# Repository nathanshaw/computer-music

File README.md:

Setup will be as follows

IAC MIDI BUS SHOUDLD BE CREATED ON MAC

CHANNELS 1-8 ARE THE FLOPPY DRIVES ON THE FIRST BUS
- pitched around C0-A3
- taken care of via an instance of MOPPY running on computer
- two arduino UNO's connected to mac VIA USB

CHANNELS 9-12 ARE THE CDROM DRIVES ON THE FIRST BUS
- midi notes split around 64 moving motor one way or another
- taken care of via python
- one arduino MEGA takes care of these 

CHANNELS 13-16 ARE THE CDROM DRIVE TREYS ON THE FIRST BUS
- any message sent will trigger the tray

CHANNELS 1-4 ARE THE STEPPERS ON THE SECOND BUS
- midi notes split around 64 moving the motor one way or another
- taken care of via python
- one arduino MEGA takes care of these 

PREREQUISITES:

sudo apt-get install python-dev libxml2-dev libxslt-dev
sudo apt-get install libasound2-dev
easy_install rtmidi-python
sudo apt-get install jack-tools ant openjdk-7-jdk fftw3 qjackctl
rtmidi python binding - pip install rtmidi-python
sudo pip install git-python
sudo pip install jira

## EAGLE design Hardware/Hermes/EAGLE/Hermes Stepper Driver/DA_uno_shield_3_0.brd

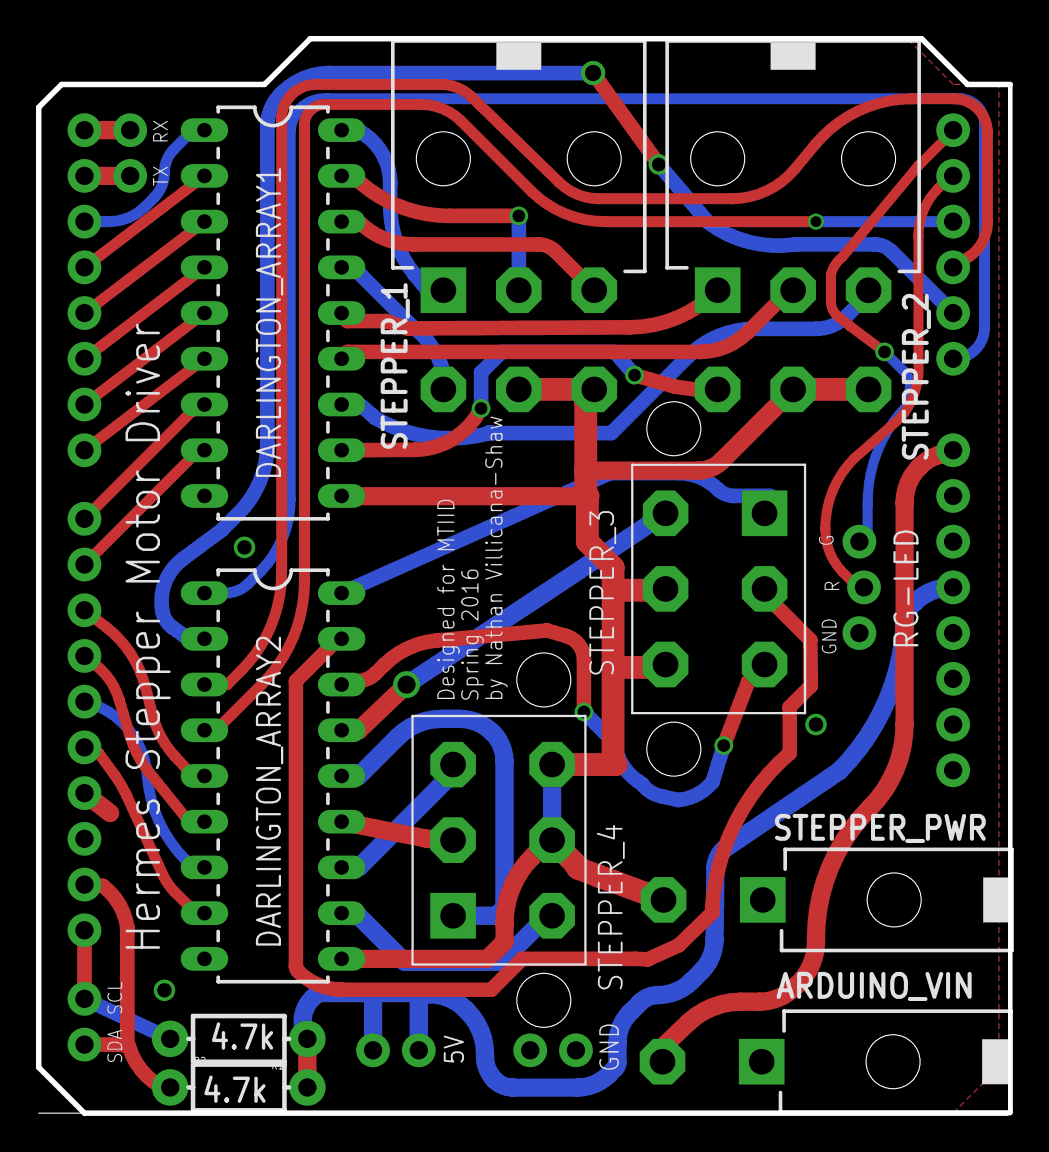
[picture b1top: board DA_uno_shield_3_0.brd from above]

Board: 2 copper layers, 54.0 x 59.7 mm, 16 parts (0 on the bottom side), 42 nets.

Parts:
5V: 1X02_NO_SILK
ARDUINO: ARDUINO_R3_SHIELD; UNO_R3_SHIELD
ARDUINO_VIN: 39-30-02?_S; 39-30-?02?
DARLINGTON_ARRAY1, DARLINGTON_ARRAY2: DIL18
GND: 1X02_NO_SILK
I2C: 1X02_NO_SILK
R1, R2: 4.7k; AXIAL-0.3-KIT
RG-LED: 1X03_LOCK_NO_SILK
SPI: 1X02_NO_SILK
STEPPER_1, STEPPER_2: 39-30-06?_S; 39-30-?06?
STEPPER_3, STEPPER_4: 39-29-06?; 39-29-?06?
STEPPER_PWR: 39-30-02?_S; 39-30-?02?

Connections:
5V: 5V.1, 5V.2, ARDUINO.5V, R1.P$1, R2.P$2
A0: ARDUINO.A0, DARLINGTON_ARRAY2.1
A1: ARDUINO.A1, DARLINGTON_ARRAY2.2
A2: ARDUINO.A2, DARLINGTON_ARRAY2.3
A3: ARDUINO.A3, DARLINGTON_ARRAY2.4
A4: ARDUINO.A4, RG-LED.2
A5: ARDUINO.A5, RG-LED.3
D10: ARDUINO.D10, DARLINGTON_ARRAY2.5
D11: ARDUINO.D11, DARLINGTON_ARRAY2.6
D12: ARDUINO.D12, DARLINGTON_ARRAY2.7
D13: ARDUINO.D13, DARLINGTON_ARRAY2.8
GND: ARDUINO.GND@0, ARDUINO.GND@1, ARDUINO.GND@2, ARDUINO_VIN.1, DARLINGTON_ARRAY1.9, DARLINGTON_ARRAY2.9, GND.1, GND.2, RG-LED.1, STEPPER_PWR.1
unnamed: DARLINGTON_ARRAY1.14, STEPPER_2.1
unnamed: DARLINGTON_ARRAY1.13, STEPPER_2.2
unnamed: DARLINGTON_ARRAY1.12, STEPPER_2.3
unnamed: DARLINGTON_ARRAY1.11, STEPPER_2.4
unnamed: ARDUINO.D6, DARLINGTON_ARRAY1.5
unnamed: ARDUINO.D7, DARLINGTON_ARRAY1.6
unnamed: ARDUINO.D8, DARLINGTON_ARRAY1.7
unnamed: ARDUINO.D9, DARLINGTON_ARRAY1.8
unnamed: DARLINGTON_ARRAY2.18, STEPPER_3.P$1
unnamed: ARDUINO.D2, DARLINGTON_ARRAY1.1
unnamed: DARLINGTON_ARRAY1.18, STEPPER_1.1
unnamed: DARLINGTON_ARRAY1.17, STEPPER_1.2
unnamed: DARLINGTON_ARRAY1.16, STEPPER_1.3
unnamed: DARLINGTON_ARRAY1.15, STEPPER_1.4
unnamed: ARDUINO.D3, DARLINGTON_ARRAY1.2
unnamed: ARDUINO.D4, DARLINGTON_ARRAY1.3
unnamed: ARDUINO.D5, DARLINGTON_ARRAY1.4
unnamed: DARLINGTON_ARRAY2.17, STEPPER_3.P$2
unnamed: DARLINGTON_ARRAY2.16, STEPPER_3.P$3
unnamed: DARLINGTON_ARRAY2.15, STEPPER_3.P$4
unnamed: DARLINGTON_ARRAY2.14, STEPPER_4.P$1
unnamed: DARLINGTON_ARRAY2.13, STEPPER_4.P$2
unnamed: DARLINGTON_ARRAY2.12, STEPPER_4.P$3
unnamed: DARLINGTON_ARRAY2.11, STEPPER_4.P$4
RX: ARDUINO.RX, SPI.1
SCL: ARDUINO.SCL, I2C.2, R1.P$2
SDA: ARDUINO.SDA, I2C.1, R2.P$1
TX: ARDUINO.TX, SPI.2
VCC: DARLINGTON_ARRAY1.10, DARLINGTON_ARRAY2.10, STEPPER_1.5, STEPPER_1.6, STEPPER_2.5, STEPPER_2.6, STEPPER_3.P$5, STEPPER_3.P$6, STEPPER_4.P$5, STEPPER_4.P$6, STEPPER_PWR.2
VIN: ARDUINO.VIN, ARDUINO_VIN.2

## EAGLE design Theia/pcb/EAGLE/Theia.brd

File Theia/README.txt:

The Theia board is an Arduino Uno shield that supports up to
8 SR-04 Ultrasonic Rangefinders.

Theia is a greek goddess and is directly translated from greek to mean “goddess” or 
“divine”. She is the mother of Helios, Selene and Eos the gods of the sun, the moon and the dawn respectively. She is the eldest daughter of Gaia and Uranus the gods of the Earth and Sky, giving her a primal origin.

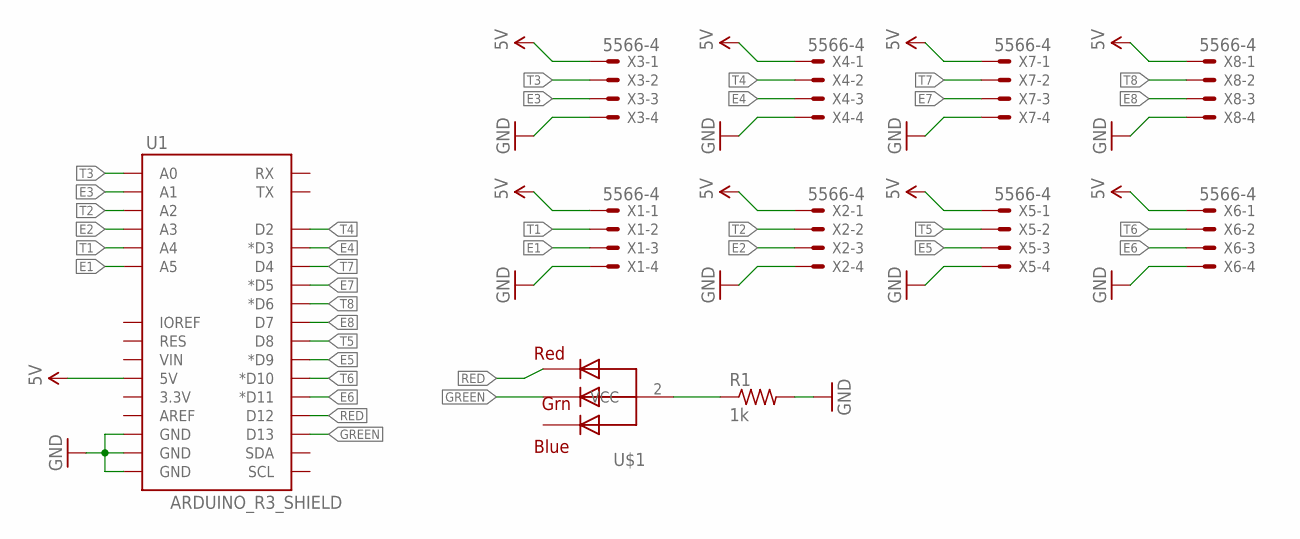
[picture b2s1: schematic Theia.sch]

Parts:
R1: 1k; 0207/7
U1: ARDUINO_R3_SHIELD; UNO_R3_SHIELD
U$1: RGBLED_CA; LED5MMRGB
X1, X2, X3, X4, X5, X6, X7, X8: 5566-4

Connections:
5V: U1.5V, X1.1, X2.1, X3.1, X4.1, X5.1, X6.1, X7.1, X8.1
E1: U1.A5, X1.3
E2: U1.A3, X2.3
E3: U1.A1, X3.3
E4: U1.D3 (*D3), X4.3
E5: U1.D9 (*D9), X5.3
E6: U1.D11 (*D11), X6.3
E7: U1.D5 (*D5), X7.3
E8: U1.D7, X8.3
GND: R1.2, U1.GND@0 (GND), U1.GND@1 (GND), U1.GND@2 (GND), X1.4, X2.4, X3.4, X4.4, X5.4, X6.4, X7.4, X8.4
GREEN: U1.D13, U$1.3 (GREEN)
unnamed: R1.1, U$1.2 (VCC)
RED: U1.D12, U$1.1 (RED)
T1: U1.A4, X1.2
T2: U1.A2, X2.2
T3: U1.A0, X3.2
T4: U1.D2, X4.2
T5: U1.D8, X5.2
T6: U1.D10 (*D10), X6.2
T7: U1.D4, X7.2
T8: U1.D6 (*D6), X8.2

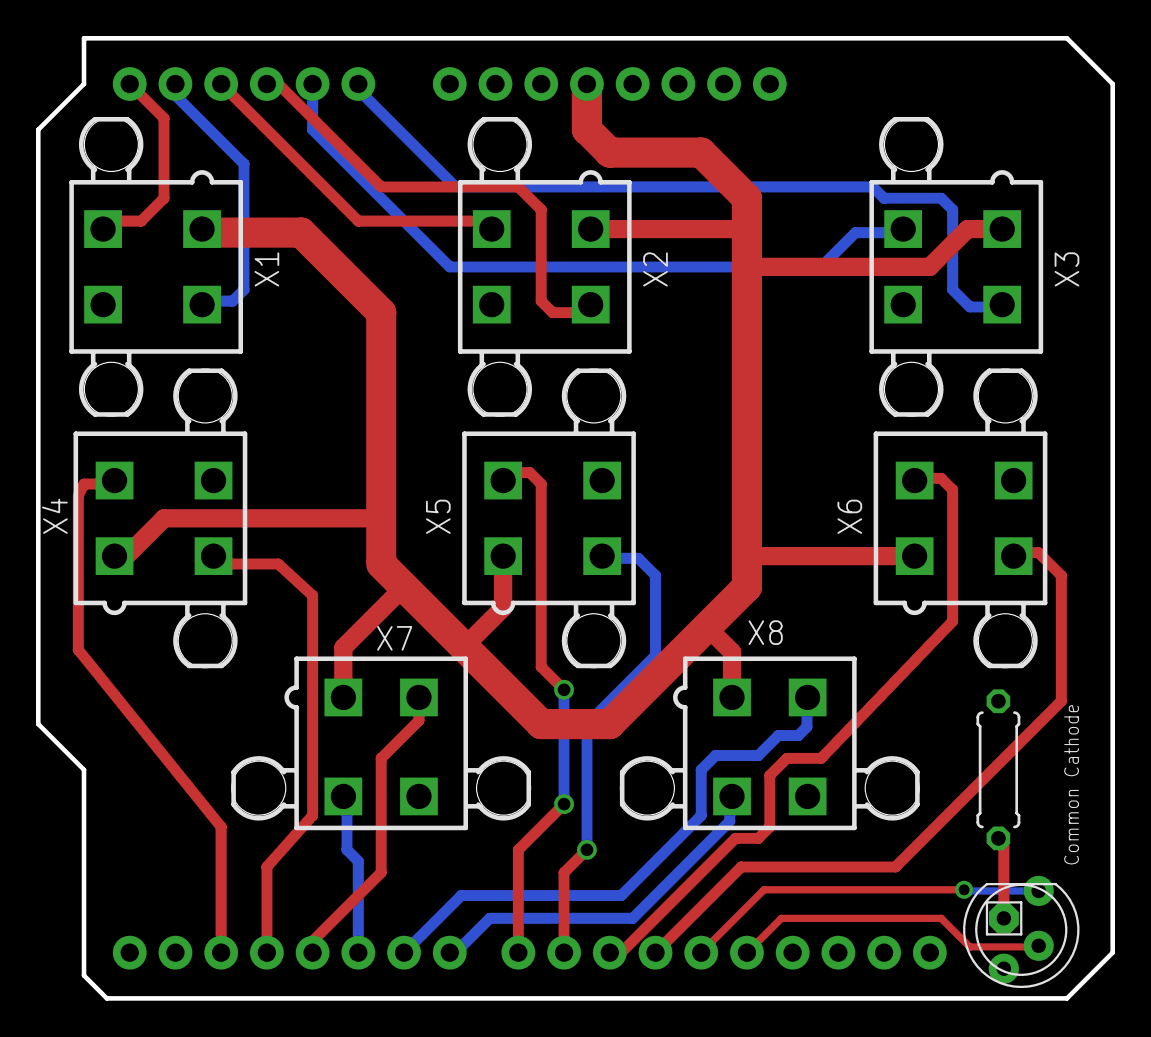
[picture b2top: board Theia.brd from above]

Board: 2 copper layers, 59.7 x 53.3 mm, 11 parts (0 on the bottom side), 21 nets.

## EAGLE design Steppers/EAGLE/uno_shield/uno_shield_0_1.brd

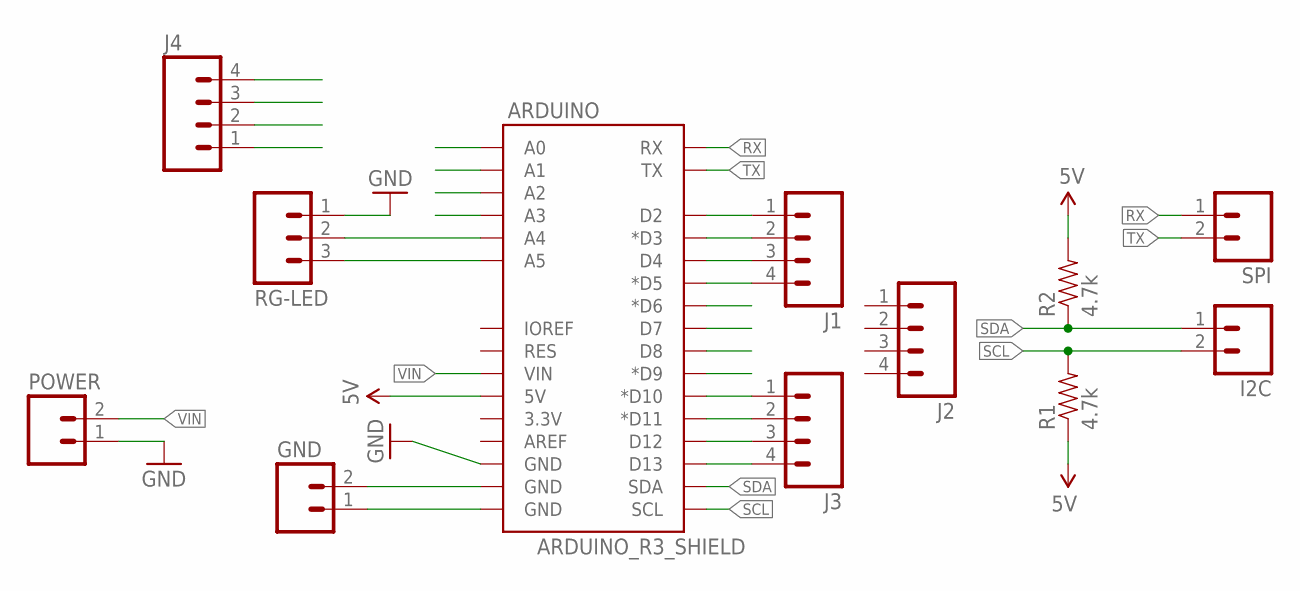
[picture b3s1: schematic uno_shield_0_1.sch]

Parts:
ARDUINO: ARDUINO_R3_SHIELD; UNO_R3_SHIELD
GND: M02LOCK_LONGPADS; 1X02_LOCK_LONGPADS
I2C: M02LOCK_LONGPADS; 1X02_LOCK_LONGPADS
J1, J2, J3, J4: M041X04_NO_SILK; 1X04_NO_SILK
POWER: M02LOCK_LONGPADS; 1X02_LOCK_LONGPADS
R1, R2: 4.7k; AXIAL-0.3-KIT
RG-LED: M03LONGPADS; 1X03_LONGPADS
SPI: M02LOCK_LONGPADS; 1X02_LOCK_LONGPADS

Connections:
5V: ARDUINO.5V, R1.P$1 (1), R2.P$2 (2)
GND: ARDUINO.GND@2 (GND), POWER.1, RG-LED.1
unnamed: ARDUINO.D2, J1.1
unnamed: ARDUINO.D3 (*D3), J1.2
unnamed: ARDUINO.D4, J1.3
unnamed: ARDUINO.D5 (*D5), J1.4
unnamed: ARDUINO.D10 (*D10), J3.1
unnamed: ARDUINO.D11 (*D11), J3.2
unnamed: ARDUINO.D12, J3.3
unnamed: ARDUINO.D13, J3.4
unnamed: ARDUINO.A4, RG-LED.2
unnamed: ARDUINO.A5, RG-LED.3
unnamed: ARDUINO.GND@1 (GND), GND.2
unnamed: ARDUINO.GND@0 (GND), GND.1
RX: ARDUINO.RX, SPI.1
SCL: ARDUINO.SCL, I2C.2, R1.P$2 (2)
SDA: ARDUINO.SDA, I2C.1, R2.P$1 (1)
TX: ARDUINO.TX, SPI.2
VIN: ARDUINO.VIN, POWER.2

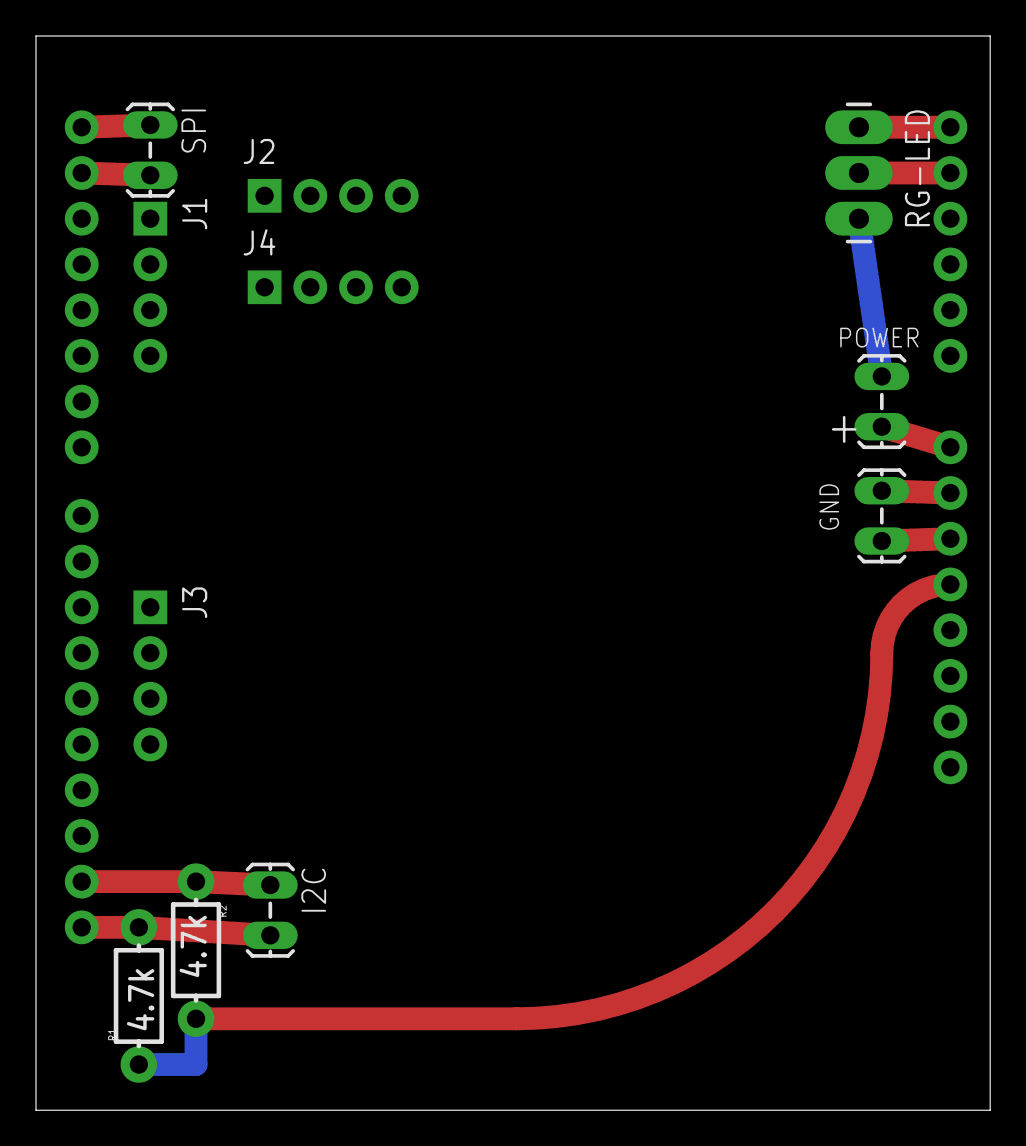
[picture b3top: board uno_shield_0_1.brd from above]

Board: 2 copper layers, 53.0 x 59.7 mm, 12 parts (0 on the bottom side), 19 nets.

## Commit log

2016-04-16 initial commit, yeeee hahgit add -Agit add -Agit add -A
2016-04-26 keeping it real, new firmware for computer music project
2016-04-26 python is now reading MIDI from IAC bus
2016-04-27 got steppers working, python working
2016-04-30 steppers alternating
2016-04-30 stable
2016-04-30 got single python script for bridging everything together
2016-05-05 stable, day before expo, about to look at trey issue
2016-05-11 expo composition stuff added
2016-05-11 revised stepper uno shield for second time
2016-06-08 starting composition for Kadenze
2016-07-03 uncommented other devices in main code and updated stepper firmware with real deal
2016-07-03 kad script
2016-07-06 first private commit, added Kadenze script for dealing the installation when used as a clock/productivity meter
2016-07-14 modified kadenze_script to not use rtmidid
2016-11-08 removed much fluff
2016-11-10 moved some things around, added meepo stuff
2016-11-13 added brigid and Theia
2016-11-14 reworked Hermes shield and Brigid code
2016-11-14 updated brigid code
2016-11-19 updated Brigid and divine council
2016-12-06 updated gitignore
2016-12-06 added Homados
2016-12-13 removed some ds_stores, removed divine council code
2016-12-13 updated brigid, moved to its own repo
2016-12-13 updated homados with v2
2017-01-18 added picture to readme
2017-01-26 added .swp's to gitignore
2017-02-07 moved some things around for the Theia board
2017-02-15 cleaning some stuff up
2017-02-15 added brigid board as a submodule
2017-02-15 added Homados as a submodule
2017-02-15 changes were made
2017-02-15 added Hermes as a submodule
2017-02-15 added No Humans Allowed as a submoduule
2017-03-10 updated no humans allowed stuff
2017-03-16 added a folder for keeping track of some general resources
2017-03-16 updated all sub-repos
2017-05-02 final push

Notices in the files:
parts and their libraries:
Nathans-Arduinos: Licensing: Creative Commons ShareAlike 4.0 International - https://creativecommons.org/licenses/by-sa/4.0
MTIID-molex-mini-fit-with-some-vertical: Copyright (C) 2011, Bob Starr
